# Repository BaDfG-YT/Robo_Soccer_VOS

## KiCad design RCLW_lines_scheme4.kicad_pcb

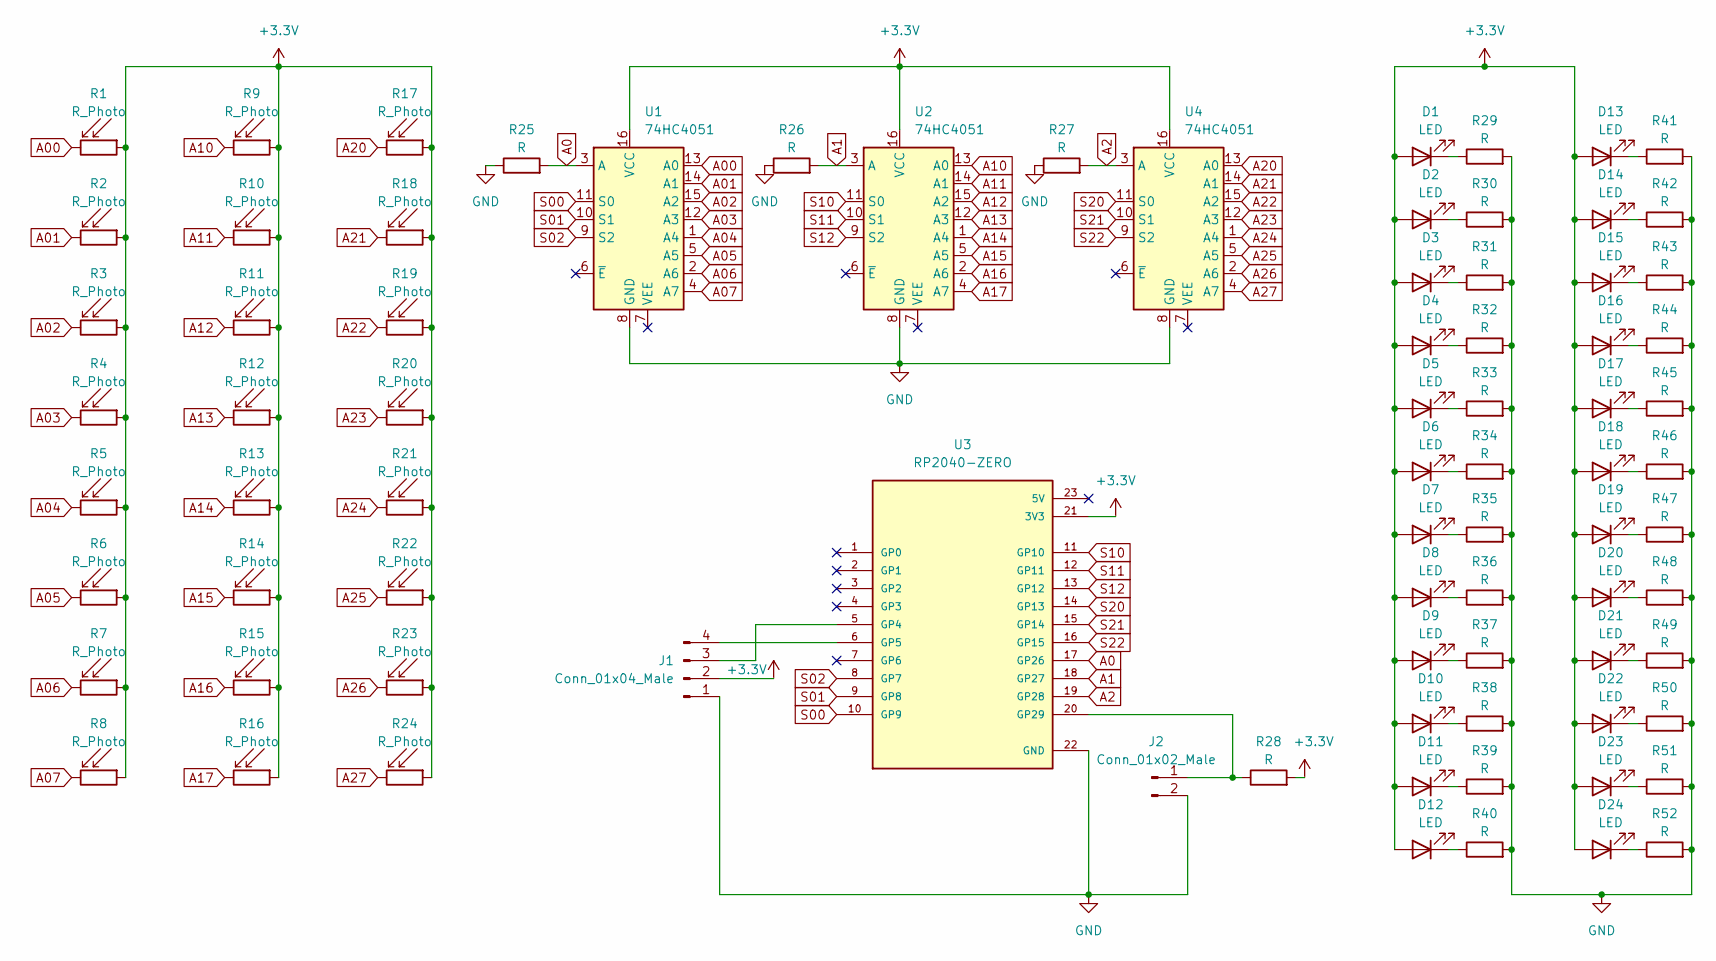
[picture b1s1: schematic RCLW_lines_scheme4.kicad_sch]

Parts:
D1, D2, D3, D4, D5, D6, D7, D8, D9, D10, D11, D12, D13, D14, D15, D16, D17, D18, D19, D20, D21, D22, D23, D24: LED; LED_0805_2012Metric_Pad1.15x1.40mm_HandSolder
J1: Conn_01x04_Male; JST_XH_B4B-XH-A_1x04_P2.50mm_Vertical
J2: Conn_01x02_Male; JST_XH_B2B-XH-A_1x02_P2.50mm_Vertical
R1, R2, R3, R4, R5, R6, R7, R8, R9, R10, R11, R12, R13, R14, R15, R16, R17, R18, R19, R20, R21, R22, R23, R24: R_Photo; R_LDR_4.9x4.2mm_P2.54mm_Vertical
R25, R26, R27, R28: R; R_0603_1608Metric_Pad0.98x0.95mm_HandSolder
R29, R30, R31, R32, R33, R34, R35, R36, R37, R38, R39, R40, R41, R42, R43, R44, R45, R46, R47, R48, R49, R50, R51, R52: R; R_0805_2012Metric_Pad1.20x1.40mm_HandSolder
U1, U2, U4: 74HC4051; SOIC-16_3.9x9.9mm_P1.27mm
U3: RP2040-ZERO; MODULE_RP2040-ZERO; PARTREV NA

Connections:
+3.3V: D1.2 (A), D2.2 (A), D3.2 (A), D4.2 (A), D5.2 (A), D6.2 (A), D7.2 (A), D8.2 (A), D9.2 (A), D10.2 (A), D11.2 (A), D12.2 (A), D13.2 (A), D14.2 (A), D15.2 (A), D16.2 (A), D17.2 (A), D18.2 (A), D19.2 (A), D20.2 (A), D21.2 (A), D22.2 (A), D23.2 (A), D24.2 (A), J1.2, R1.1, R2.1, R3.1, R4.1, R5.1, R6.1, R7.1, R8.1, R9.1, R10.1, R11.1, R12.1, R13.1, R14.1, R15.1, R16.1, R17.1, R18.1, R19.1, R20.1, R21.1, R22.1, R23.1, R24.1, R28.2, U1.16 (VCC), U2.16 (VCC), U3.21 (3V3), U4.16 (VCC); also elsewhere on the board
A0: R25.2, U1.3 (A), U3.17 (GP26)
A00: R1.2, U1.13 (A0)
A01: R2.2, U1.14 (A1)
A1: R26.2, U2.3 (A), U3.18 (GP27); also elsewhere on the board
A02: R3.2, U1.15 (A2)
A03: R4.2, U1.12 (A3)
A04: R5.2, U1.1 (A4)
A05: R6.2, U1.5 (A5)
A06: R7.2, U1.2 (A6)
A07: R8.2, U1.4 (A7)
A10: R9.2, U2.13 (A0); also elsewhere on the board
A11: R10.2, U2.14 (A1); also elsewhere on the board
A12: R11.2, U2.15 (A2); also elsewhere on the board
A13: R12.2, U2.12 (A3); also elsewhere on the board
A14: R13.2, U2.1 (A4); also elsewhere on the board
A15: R14.2, U2.5 (A5); also elsewhere on the board
A16: R15.2, U2.2 (A6); also elsewhere on the board
A17: R16.2, U2.4 (A7); also elsewhere on the board
A20: R17.2, U4.13 (A0); also elsewhere on the board
A21: R18.2, U4.14 (A1); also elsewhere on the board
A22: R19.2, U4.15 (A2); also elsewhere on the board
A23: R20.2, U4.12 (A3); also elsewhere on the board
A24: R21.2, U4.1 (A4); also elsewhere on the board
A25: R22.2, U4.5 (A5); also elsewhere on the board
A26: R23.2, U4.2 (A6); also elsewhere on the board
A27: R24.2, U4.4 (A7); also elsewhere on the board
unnamed: D1.1 (K), R29.1
unnamed: D2.1 (K), R30.1
unnamed: D3.1 (K), R31.1
unnamed: D4.1 (K), R32.1
unnamed: D5.1 (K), R33.1
unnamed: D6.1 (K), R34.1
unnamed: D7.1 (K), R35.1
unnamed: D8.1 (K), R36.1
unnamed: D9.1 (K), R37.1
unnamed: D10.1 (K), R38.1
unnamed: D11.1 (K), R39.1
unnamed: D12.1 (K), R40.1
unnamed: D13.1 (K), R41.1
unnamed: D14.1 (K), R42.1
unnamed: D15.1 (K), R43.1
unnamed: D16.1 (K), R44.1
unnamed: D17.1 (K), R45.1
unnamed: D18.1 (K), R46.1
unnamed: D19.1 (K), R47.1
unnamed: D20.1 (K), R48.1
unnamed: D21.1 (K), R49.1
unnamed: D22.1 (K), R50.1
unnamed: D23.1 (K), R51.1
unnamed: D24.1 (K), R52.1
unnamed 51: J1.3, U3.5 (GP4); also elsewhere on the board
unnamed 52: J1.4, U3.6 (GP5); also elsewhere on the board
unnamed 53: J2.1, R28.1, U3.20 (GP29); also elsewhere on the board
S00: U1.11 (S0), U3.10 (GP9)
S01: U1.10 (S1), U3.9 (GP8)
S02: U1.9 (S2), U3.8 (GP7)
S10: U2.11 (S0), U3.11 (GP10); also elsewhere on the board
S11: U2.10 (S1), U3.12 (GP11); also elsewhere on the board
S12: U2.9 (S2), U3.13 (GP12); also elsewhere on the board
S20: U3.14 (GP13), U4.11 (S0); also elsewhere on the board
S21: U3.15 (GP14), U4.10 (S1); also elsewhere on the board
S22: U3.16 (GP15), U4.9 (S2); also elsewhere on the board

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
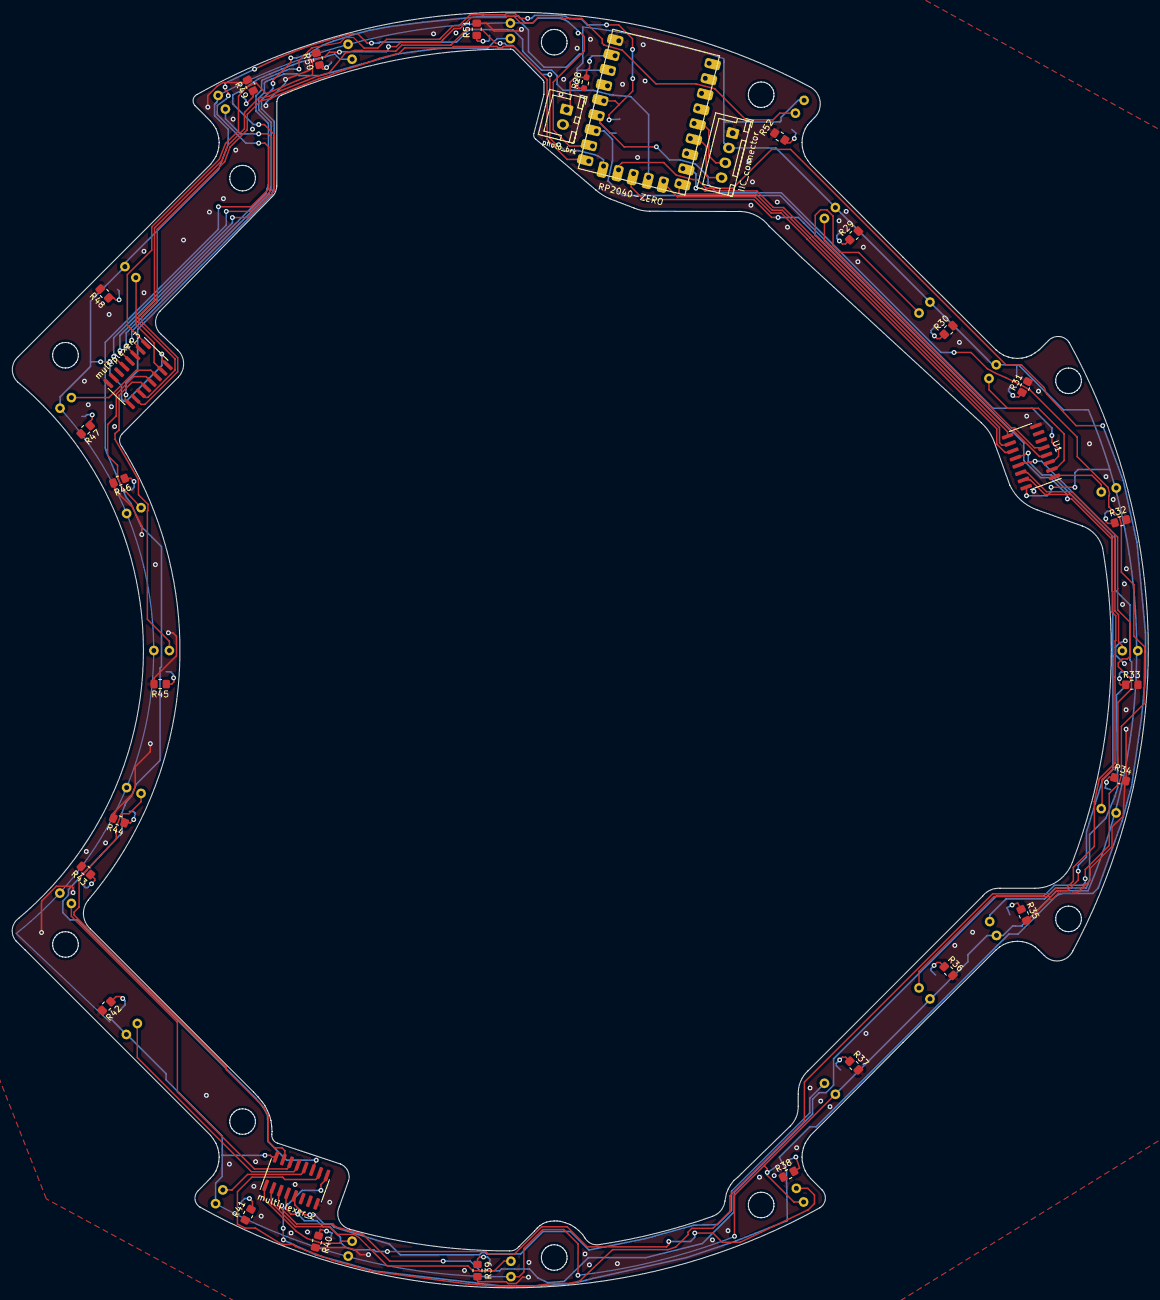
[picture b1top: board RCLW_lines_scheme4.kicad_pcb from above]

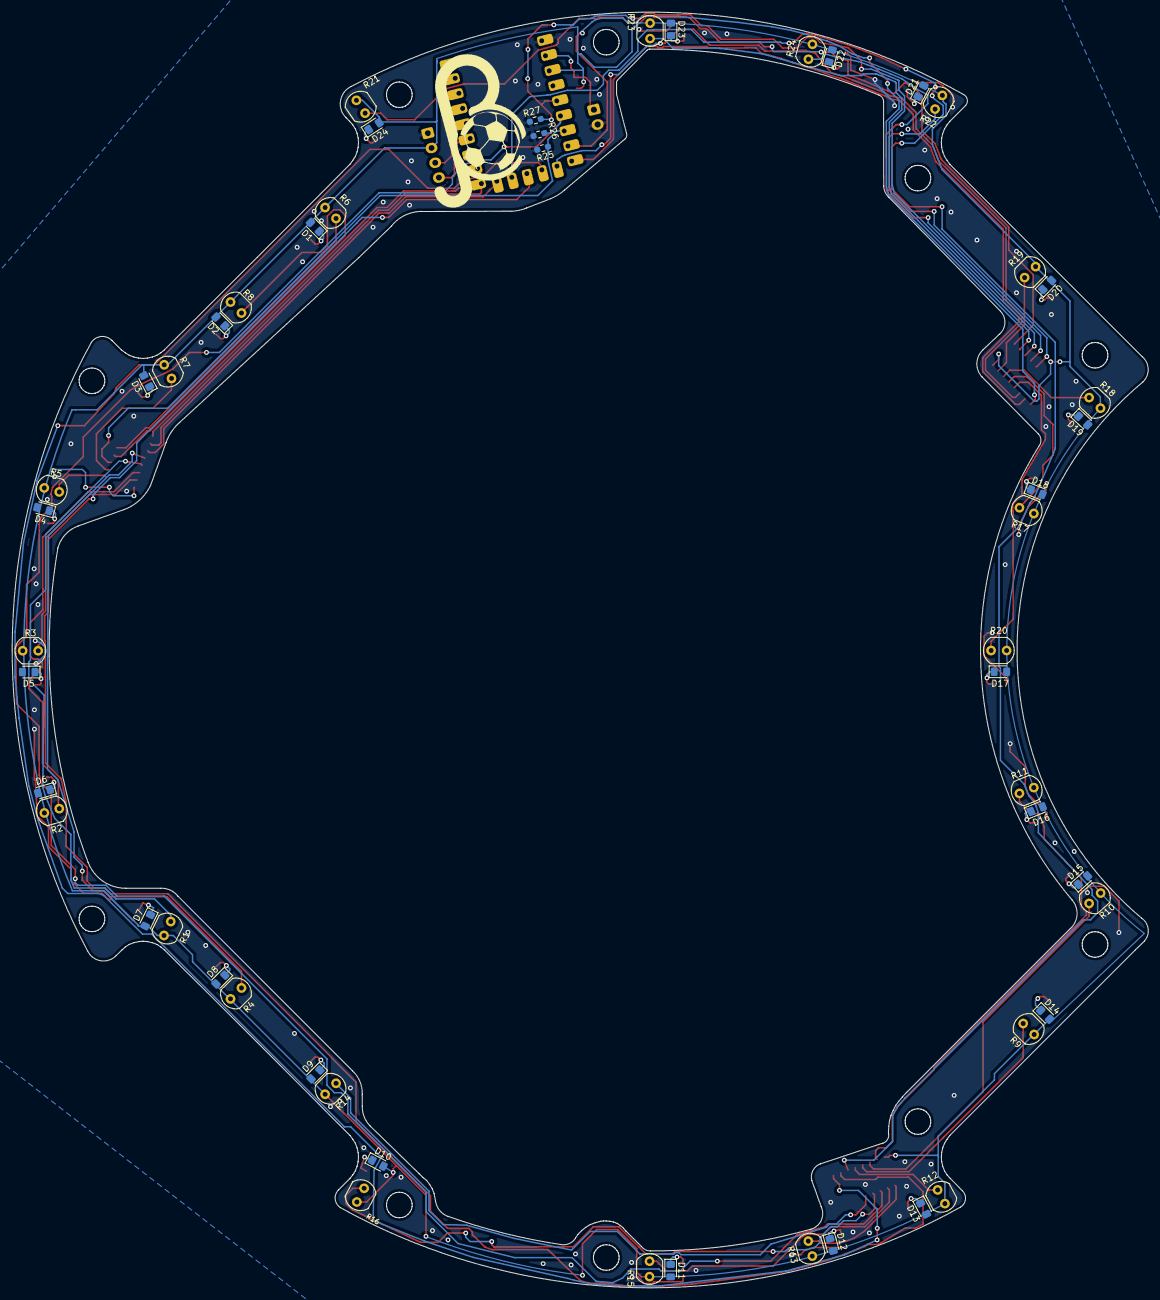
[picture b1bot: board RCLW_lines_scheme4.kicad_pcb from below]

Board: 2 copper layers, 186.1 x 209.0 mm, 82 parts (51 on the bottom side), 65 nets.

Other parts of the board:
IIC_connector: Conn_01x04_Male; JST_XH_B4B-XH-A_1x04_P2.50mm_Vertical
multiplexer_2, multiplexer_3: 74HC4051; SOIC-16_3.9x9.9mm_P1.27mm
photo_brk: Conn_01x02_Male; JST_XH_B2B-XH-A_1x02_P2.50mm_Vertical

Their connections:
+3.3V: IIC_connector.2, multiplexer_2.16 (VCC), multiplexer_3.16 (VCC); also elsewhere on the board
A1: multiplexer_2.3 (A); also elsewhere on the board
A10: multiplexer_2.13 (A0); also elsewhere on the board
A11: multiplexer_2.14 (A1); also elsewhere on the board
A12: multiplexer_2.15 (A2); also elsewhere on the board
A13: multiplexer_2.12 (A3); also elsewhere on the board
A14: multiplexer_2.1 (A4); also elsewhere on the board
A15: multiplexer_2.5 (A5); also elsewhere on the board
A16: multiplexer_2.2 (A6); also elsewhere on the board
A17: multiplexer_2.4 (A7); also elsewhere on the board
A20: multiplexer_3.13 (A0); also elsewhere on the board
A21: multiplexer_3.14 (A1); also elsewhere on the board
A22: multiplexer_3.15 (A2); also elsewhere on the board
A23: multiplexer_3.12 (A3); also elsewhere on the board
A24: multiplexer_3.1 (A4); also elsewhere on the board
A25: multiplexer_3.5 (A5); also elsewhere on the board
A26: multiplexer_3.2 (A6); also elsewhere on the board
A27: multiplexer_3.4 (A7); also elsewhere on the board
unnamed 51: IIC_connector.3; also elsewhere on the board
unnamed 52: IIC_connector.4; also elsewhere on the board
unnamed 53: photo_brk.1; also elsewhere on the board
S10: multiplexer_2.11 (S0); also elsewhere on the board
S11: multiplexer_2.10 (S1); also elsewhere on the board
S12: multiplexer_2.9 (S2); also elsewhere on the board
S20: multiplexer_3.11 (S0); also elsewhere on the board
S21: multiplexer_3.10 (S1); also elsewhere on the board
S22: multiplexer_3.9 (S2); also elsewhere on the board
